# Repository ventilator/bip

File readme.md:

# BIP

## A 40C3 CHARACTER, REIMAGINED AS A PCB

BIP is a character from the [40C3 style guide](https://events.ccc.de/congress/2026/infos/styleguide/), reincarnated as a 70 x 70 mm PCB.

Solder kits will be available at 40C3 at the [Binary Kitchen assembly](https://www.binary-kitchen.de/).

Designed with [Alber PCB Designer](https://alber.me/miscellaneous/tools/pcb-designer.html), this project includes the tool's [`bip-project.json`](./bip-project.json), KiCad exports, fabrication files, visual assets, and an interactive BOM.

## BOARD AT A GLANCE

- 70 x 70 mm PCB outline
- Green soldermask and white silkscreen styling
- JLCPCB-ready manufacturing metadata and board setup
- KiCad source project plus generated Gerber outputs
- Interactive assembly review with the HTML BOM

## PROJECT FILES

- [Interactive BOM](./ibom.html)
- [Full board render](./bip-view.png)
- [KiCad project](./bip-kicad/)
- [Gerber package](./bip-gerber.zip)
- [KiCad bundle archive](./bip-kicad.zip)
- [PCB metadata](./bip-project.json)
- [Vector artwork](./bip.svg)
- [Small PNG artwork](./bip-icon.png)
- [Animation preview](./bip.mp4)
- [Envelope print file](./bip_125mm_envelope.pdf)
- [Packaging photo 1](./bip-packaging-1.webp)
- [Packaging photo 2](./bip-packaging-2.webp)

## IN THIS DIRECTORY

This directory contains the canonical design source and the exported deliverables for the BIP board:

- `bip-kicad/` holds the editable KiCad project files.
- `ibom.html` is the interactive BOM view for checking component placement and values.
- `bip-gerber.zip` contains the manufacturing Gerber files.
- `bip-project.json` captures the board metadata and manufacturing setup.
- `bip-view.png`, `bip-view-thumb.png`, and `bip-view-backside-thumb.png` provide render previews for documentation and presentation.
- `bip.svg`, `bip-icon.png`, `bip.mp4`, `bip-loop.gif`, the two `bip-packaging-*.webp` photos, and `bip_125mm_envelope.pdf` provide additional visual and print assets.

The [BIP vector artwork](./bip.svg) is used as a visual accent in this README.

## DESIGN WORKFLOW

The [KiCad project files](./bip-kicad/) are available for inspection and downstream use. For design iteration, use the [Alber PCB Designer](https://alber.me/miscellaneous/tools/pcb-designer.html) with the included [`bip-project.json`](./bip-project.json); the KiCad files are an export, not the source workflow. Open the [interactive BOM](./ibom.html) to inspect component placement and values. For fabrication, use the generated Gerber package or the bundled archive alongside the board metadata file.

## LICENSE

The original hardware design files are licensed under [CC BY-NC-SA 4.0](./LICENSE.md).

## PACKAGING

A semi transparent envelope 125mm x 125mm

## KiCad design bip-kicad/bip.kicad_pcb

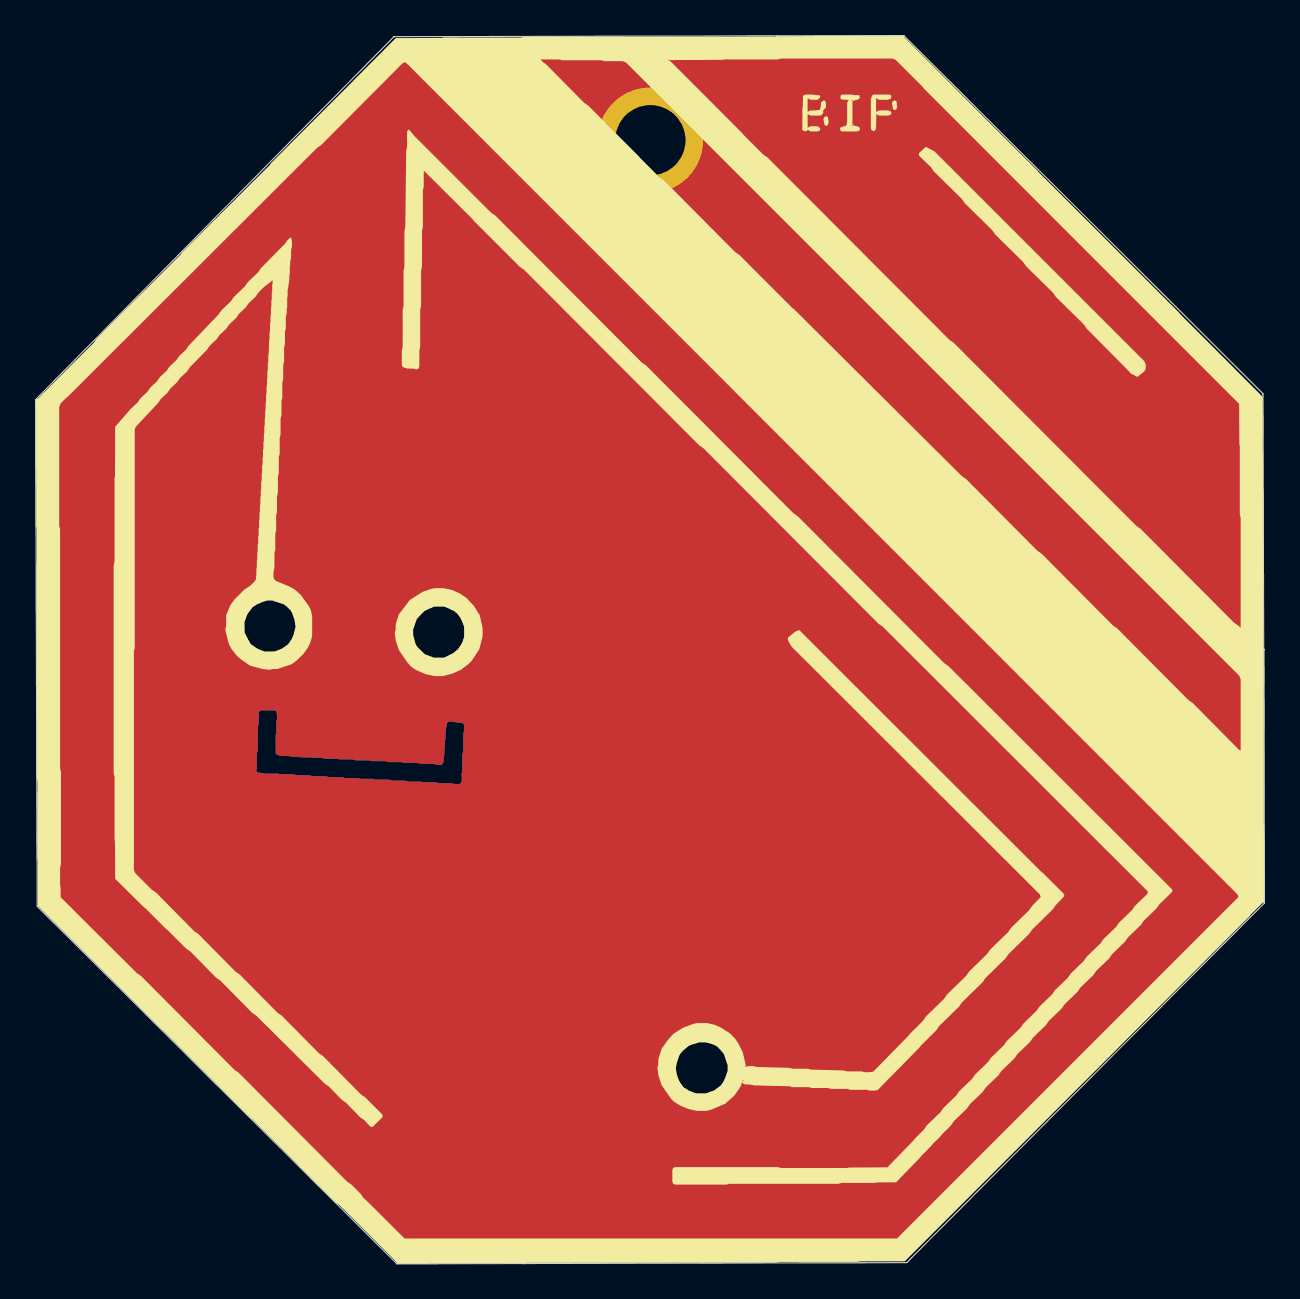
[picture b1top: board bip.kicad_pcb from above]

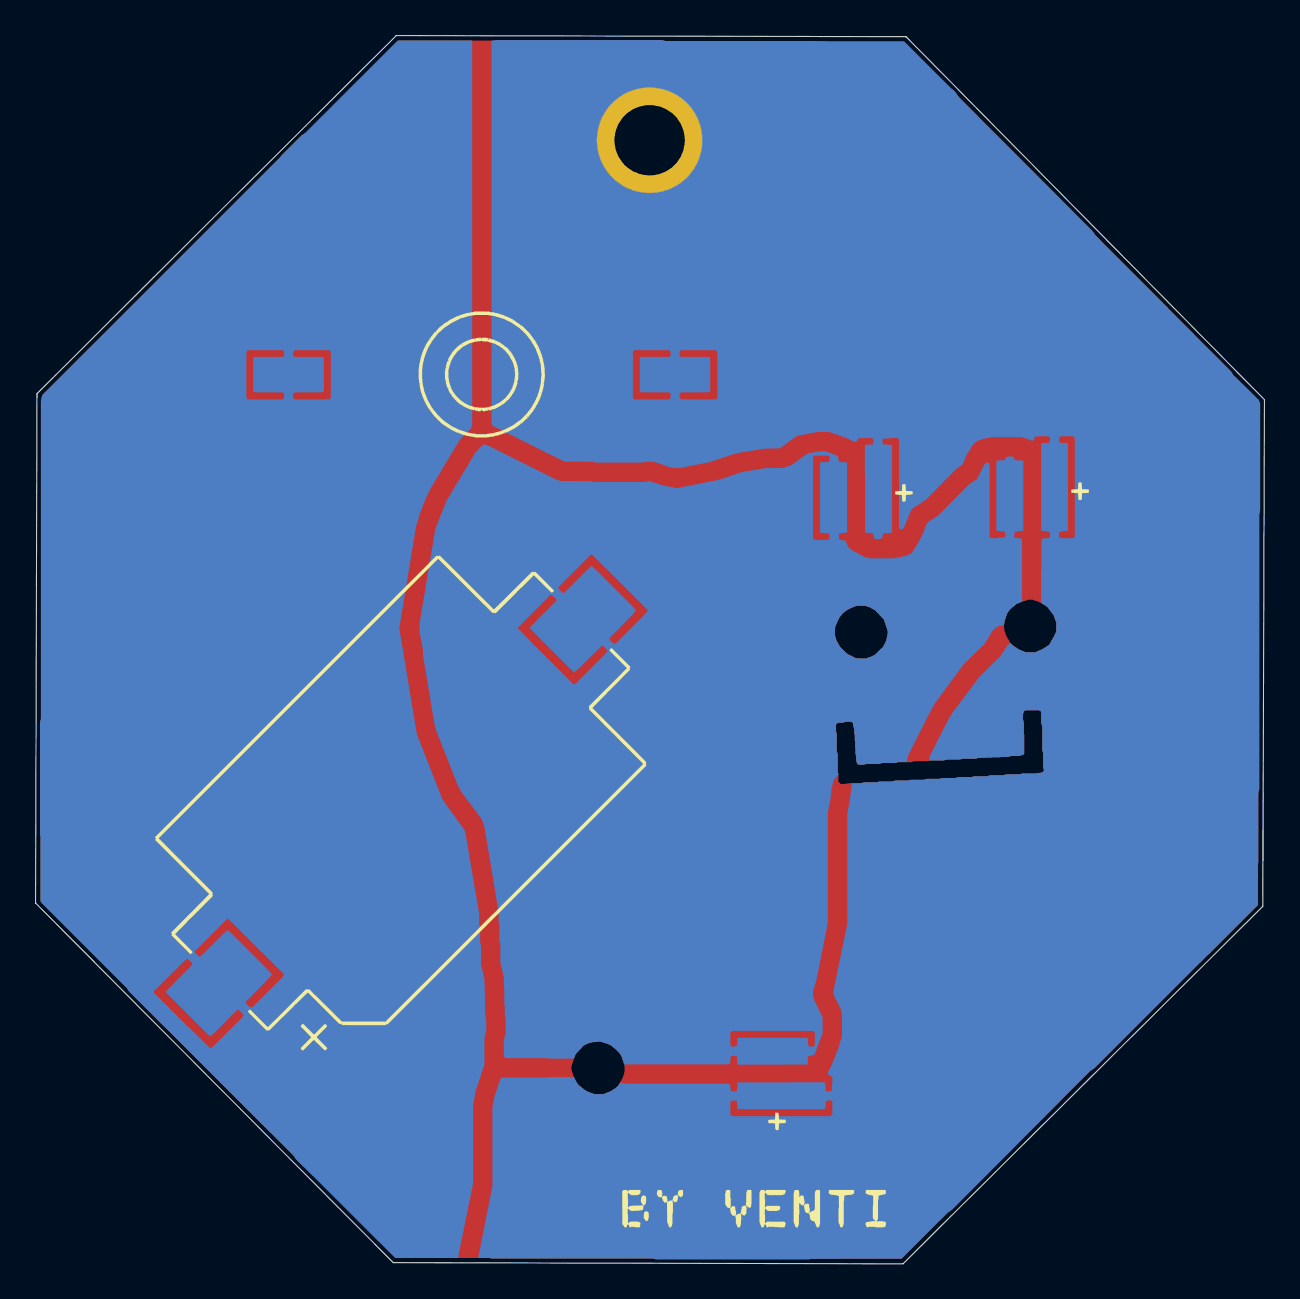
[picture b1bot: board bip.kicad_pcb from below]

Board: 2 copper layers, 69.9 x 69.9 mm, 5 parts (5 on the bottom side), 2 nets, no tracks yet.

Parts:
BAT 1: BAT; battery
LED 1, LED 2, LED 3: LED; led
SW 1: SW; button

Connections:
GND: BAT 1.-, LED 1.K, LED 2.K, LED 3.K
VCC: LED 1.A, LED 2.A, LED 3.A
